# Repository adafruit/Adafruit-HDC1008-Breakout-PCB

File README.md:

## Adafruit HDC1008 Breakout PCB

<a href="http://www.adafruit.com/products/2635"><br/>
Click here to purchase one from the Adafruit shop</a>

PCB files for the Adafruit HDC1008 Breakout. Format is EagleCAD schematic and board layout
* https://www.adafruit.com/products/2635

### DESCRIPTION
It's summer and you're sweating and your hair's all frizzy and all you really want to know is why the weatherman said this morning that today's relative humidity would max out at a perfectly reasonable 52% when it feels more like 77%. Enter the HDC1008 Temperature + Humidity Sensor - the best way to prove the weatherman wrong!

This I2C digital humidity sensor is a fairly accurate and intelligent alternative to the much simpler Humidity and Temperature Sensor - SHT15 Breakout It has a typical accuracy of ±4% with an operating range that's optimized from 10% to 80% RH. Operation outside this range is still possible - just the accuracy might drop a bit. The temperature output has a typical accuracy of ±0.2°C from -20~85°C.

The HDC1008 sensor chip has 2 address-select pins, so you can have up to 4 shared on a single I2C bus. It's also 3-5V power and logic safe so you don't need any level shifters or regulators to use with a 5V or 3V microcontroller.

Such a lovely chip, but only available in a tiny BGA package. So we spun up a breakout board with the chip and some extra passive components to make it easy to use. Each order comes with one fully assembled and tested PCB breakout and a small piece of header. You'll need to solder the header onto the PCB but it's fairly easy and takes only a few minutes even for a beginner.

### License

Adafruit invests time and resources providing this open source design, please support Adafruit and open-source hardware by purchasing products from [Adafruit.com](https://www.adafruit.com)!

Designed by Adafruit Industries. 

Creative Commons Attribution, Share-Alike license, check license.txt for more information All text above must be included in any redistribution - see license.txt for more information.

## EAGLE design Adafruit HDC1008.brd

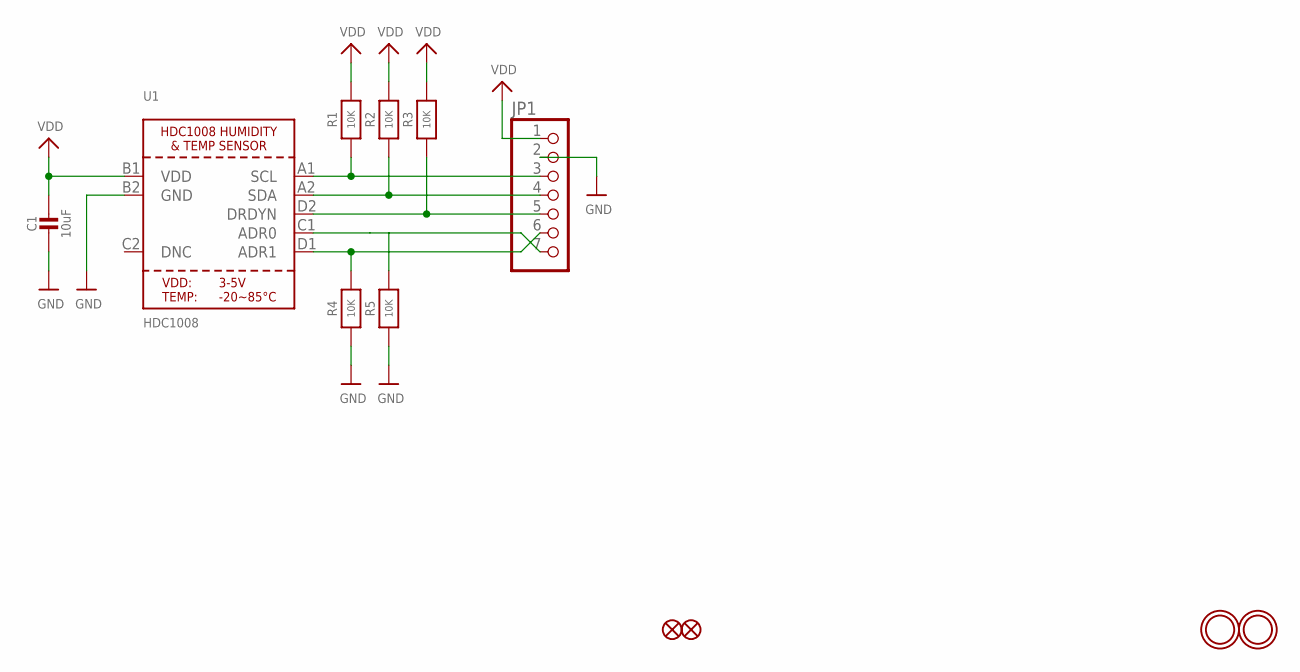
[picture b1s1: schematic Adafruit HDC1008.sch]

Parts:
C1: 10uF; 0805-NO
FID1, FID2: FIDUCIAL""; FIDUCIAL_1MM
JP1: HEADER-1X770MIL; 1X07_ROUND_70
R1, R3, R4, R5: 10K; 0805-NO
R2: 10K; _0805MP
U1: HDC1008; DSBGA8_HDC1008
U$2, U$3: MOUNTINGHOLE2.5; MOUNTINGHOLE_2.5_PLATED

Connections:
A0: JP1.7, R5.2, U1.C1 (ADR0)
A1: JP1.6, R4.2, U1.D1 (ADR1)
GND: C1.2, JP1.2, R4.1, R5.1, U1.B2 (GND)
RDY: JP1.5, R3.1, U1.D2 (DRDYN)
SCL: JP1.3, R1.1, U1.A1 (SCL)
SDY: JP1.4, R2.1, U1.A2 (SDA)
VDD: C1.1, JP1.1, R1.2, R2.2, R3.2, U1.B1 (VDD)

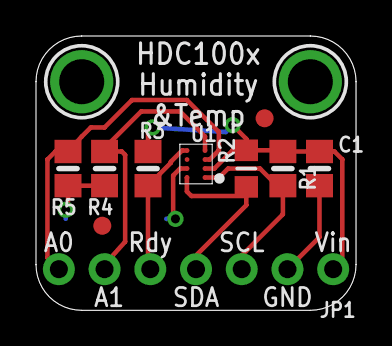
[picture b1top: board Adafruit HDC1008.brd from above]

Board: 2 copper layers, 17.8 x 15.2 mm, 13 parts (1 on the bottom side), 7 nets.

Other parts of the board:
U$14: ADAFRUIT_3.5MM

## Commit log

2016-09-28 init

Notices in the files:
parts and their libraries:
microbuilder: This work is placed in the public domain, and may be freely used for commercial and non-commercial work with the following conditions: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
